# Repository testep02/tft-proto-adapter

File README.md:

TFT-Proto Adapters
=================================================================================
The files in this repository are schematics and boards for use in Eagle that provide an easy connection for the TFT-Proto from MikroE to the STM32F4 Discovery. There are 3 different variations of the board in this repository. All of these designs have been verified to work. They can easily be printed through OshPark.

Features
---------------------------------------------------------------------------------
-  TFT backlight connected to a pin to allow PWM control
-  Backlight powered from 5V instead of 3.3V to allow for brighter viewing
-  Backlight controlled through a transistor to prevent driving the LEDs directly from a pin
-  Reset pin also routed through a transistor and connected to a pin for software control

Variations
---------------------------------------------------------------------------------
-  16-bit FSMC Portrait
	-  This version of the board mounts the TFT in portrait mode
	-  The connection to the STM32F4 Discovery is 16-bit parallel and uses FSMC.
-  16-Bit FSMC Landscape
	-  Same as the above variation, except with this one the board is laid out so that the screen is in landscape configuration. This is the variatioon I use.
-  16-bit GPIO
	-  Uses entire GPIOE port for data lines
	-  Uses sme pins on the GPIOB port for control
	-  IM[3:0] are connected to header pins to allow configuration between 16-bit and 8-bit
	-  Is not connected to the FSMC pins, so bit-banging is required

Code Examples
---------------------------------------------------------------------------------
Examples of driving the TFT-Proto can be found in my other repository. The drivers include all init code and basic drawing functions.

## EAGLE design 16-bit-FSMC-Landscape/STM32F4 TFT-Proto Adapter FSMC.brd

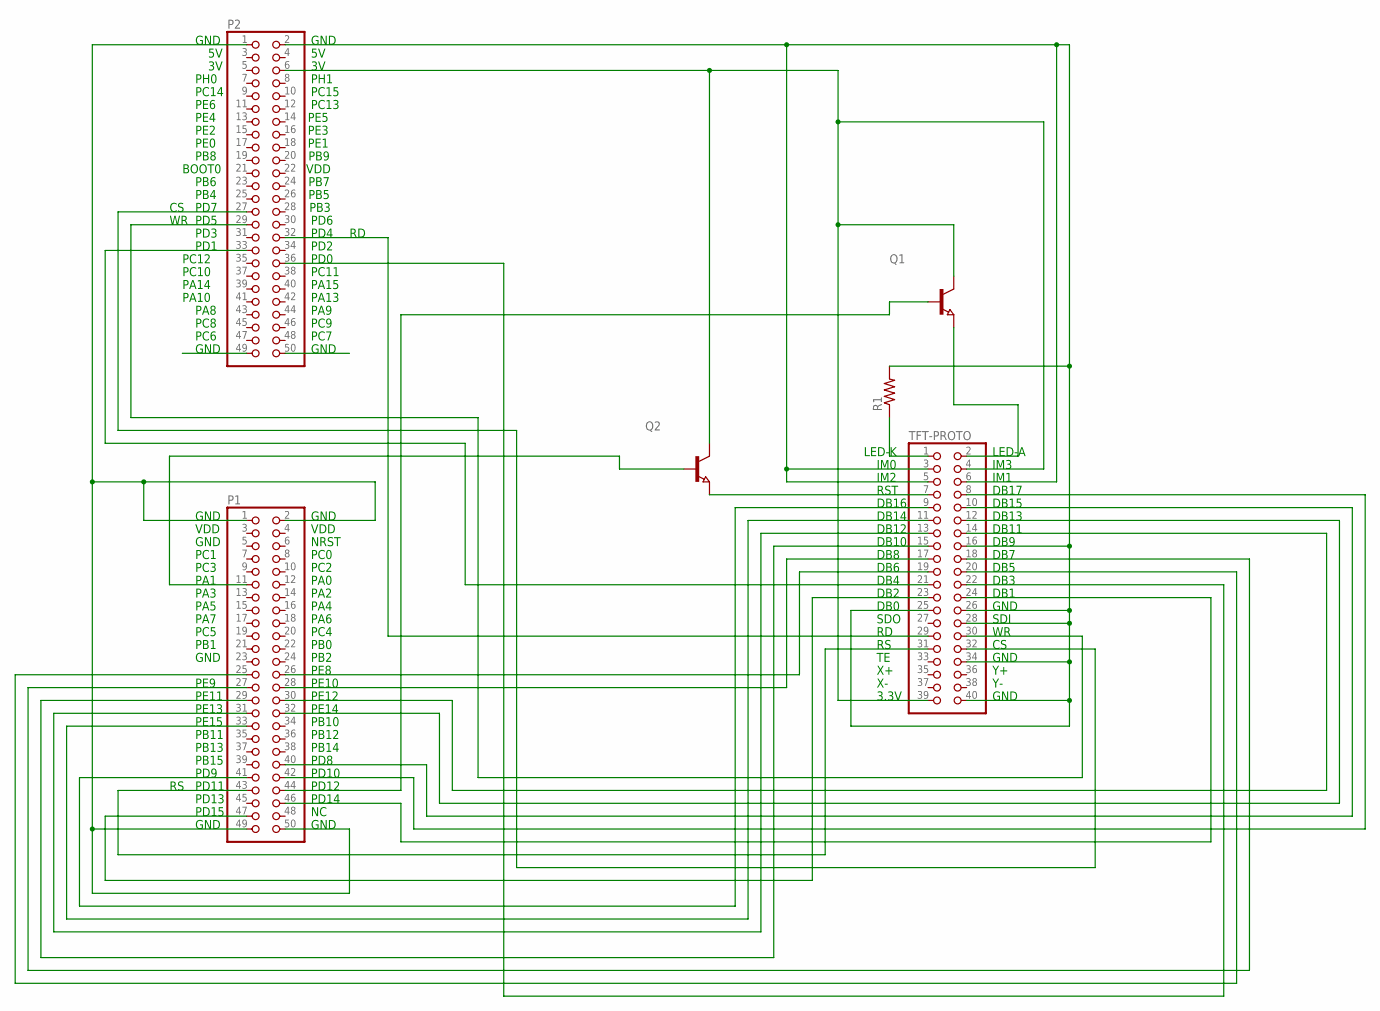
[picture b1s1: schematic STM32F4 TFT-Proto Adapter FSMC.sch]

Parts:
P1, P2: PINHD-2X25; 2X25
Q1, Q2: NPN-TRANSISTOR_SOT23; SOT23
R1: R-US_R0805; R0805
TFT-PROTO: PINHD-2X20; 2X20

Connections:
CS: P2.27, TFT-PROTO.32
DB1: P1.46, TFT-PROTO.24
DB2: P1.47, TFT-PROTO.23
DB3: P2.36, TFT-PROTO.22
DB4: P2.33, TFT-PROTO.21
DB5: P1.25, TFT-PROTO.20
DB6: P1.26, TFT-PROTO.19
DB7: P1.27, TFT-PROTO.18
DB8: P1.28, TFT-PROTO.17
DB10: P1.29, TFT-PROTO.15
DB11: P1.30, TFT-PROTO.14
DB12: P1.31, TFT-PROTO.13
DB13: P1.32, TFT-PROTO.12
DB14: P1.33, TFT-PROTO.11
DB15: P1.40, TFT-PROTO.10
DB16: P1.41, TFT-PROTO.9
DB17: P1.42, TFT-PROTO.8
GND: P1.1, P1.2, P1.49, P1.50, P2.1, P2.2, P2.49, P2.50, R1.2, TFT-PROTO.3, TFT-PROTO.5, TFT-PROTO.6, TFT-PROTO.16, TFT-PROTO.25, TFT-PROTO.26, TFT-PROTO.28, TFT-PROTO.34, TFT-PROTO.40
unnamed: P1.44, Q1.1 (B)
unnamed: R1.1, TFT-PROTO.1
unnamed: Q1.2 (E), TFT-PROTO.2
unnamed: Q2.2 (E), TFT-PROTO.7
PWR: P2.6, Q1.3 (C), Q2.3 (C), TFT-PROTO.4, TFT-PROTO.39
RD: P2.32, TFT-PROTO.29
RS: P1.43, TFT-PROTO.31
RST: P1.11, Q2.1 (B)
WR: P2.29, TFT-PROTO.30

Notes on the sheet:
GND
PH0
PH1
PC14
PC15
PE6
PC13
PE4 PE5
PE2 PE3
PE0 PE1
PB8 PB9
BOOT0 VDD
PB6 PB7
PB4 PB5
PD7 PB3
PD5
PD3
PD1
PC12
PC10
PA14
PA10
PA8
PC8
PC6
PC7
PC9
PA9
PA13
PA15
PC11
PD0
PD2
PD4
PD6
PD15
PD13
PD11
PD9
PB15

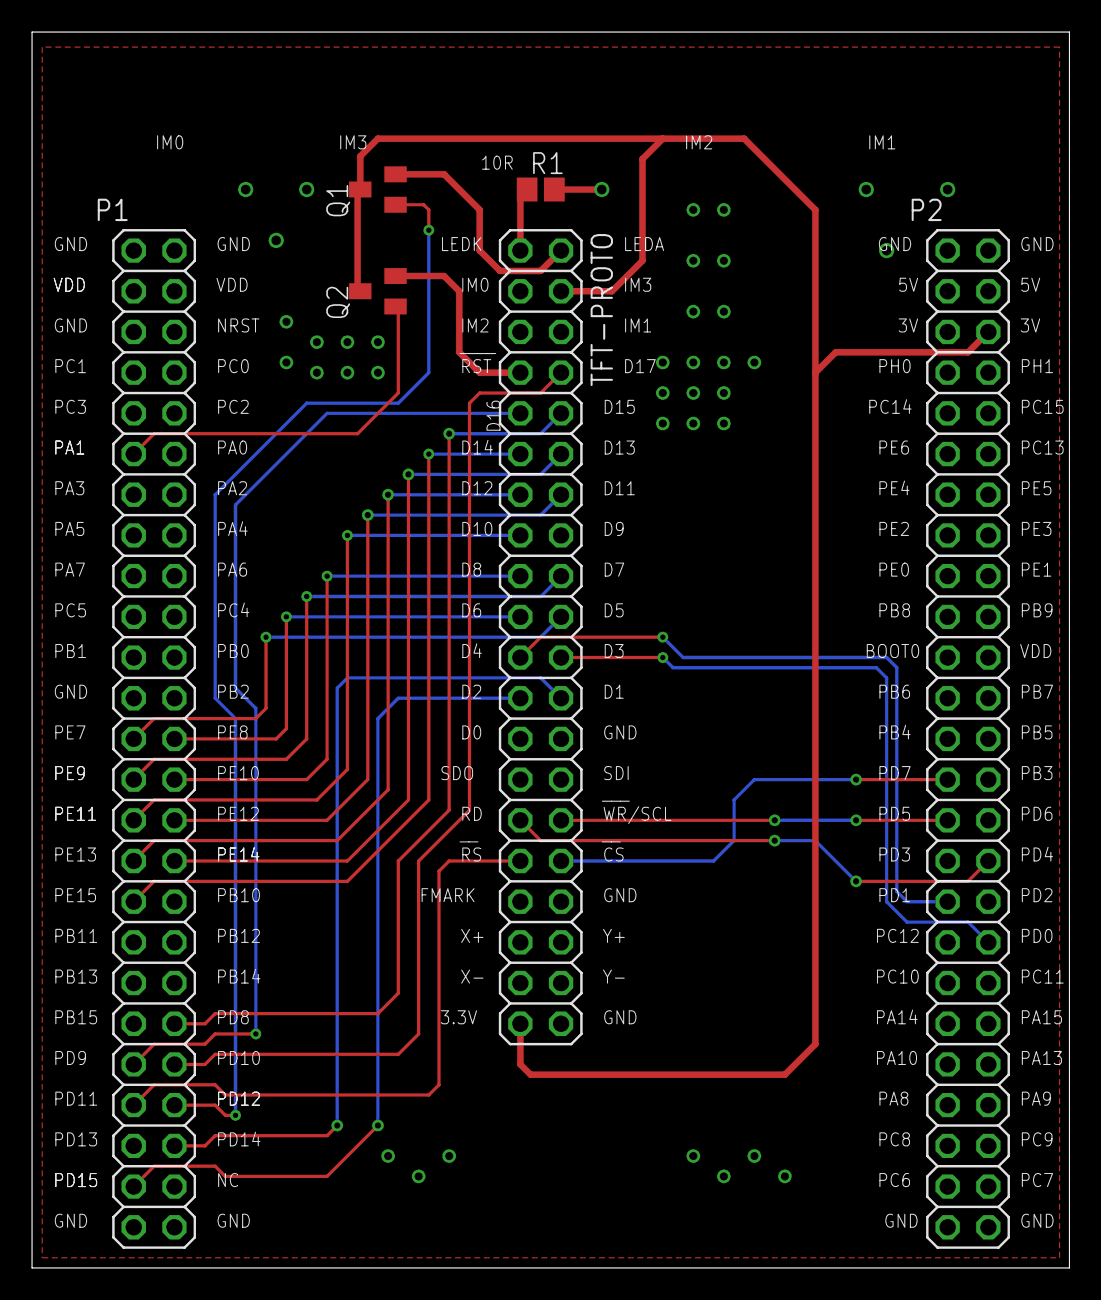
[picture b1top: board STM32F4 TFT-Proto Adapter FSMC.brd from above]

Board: 2 copper layers, 64.8 x 77.1 mm, 6 parts (0 on the bottom side), 27 nets.

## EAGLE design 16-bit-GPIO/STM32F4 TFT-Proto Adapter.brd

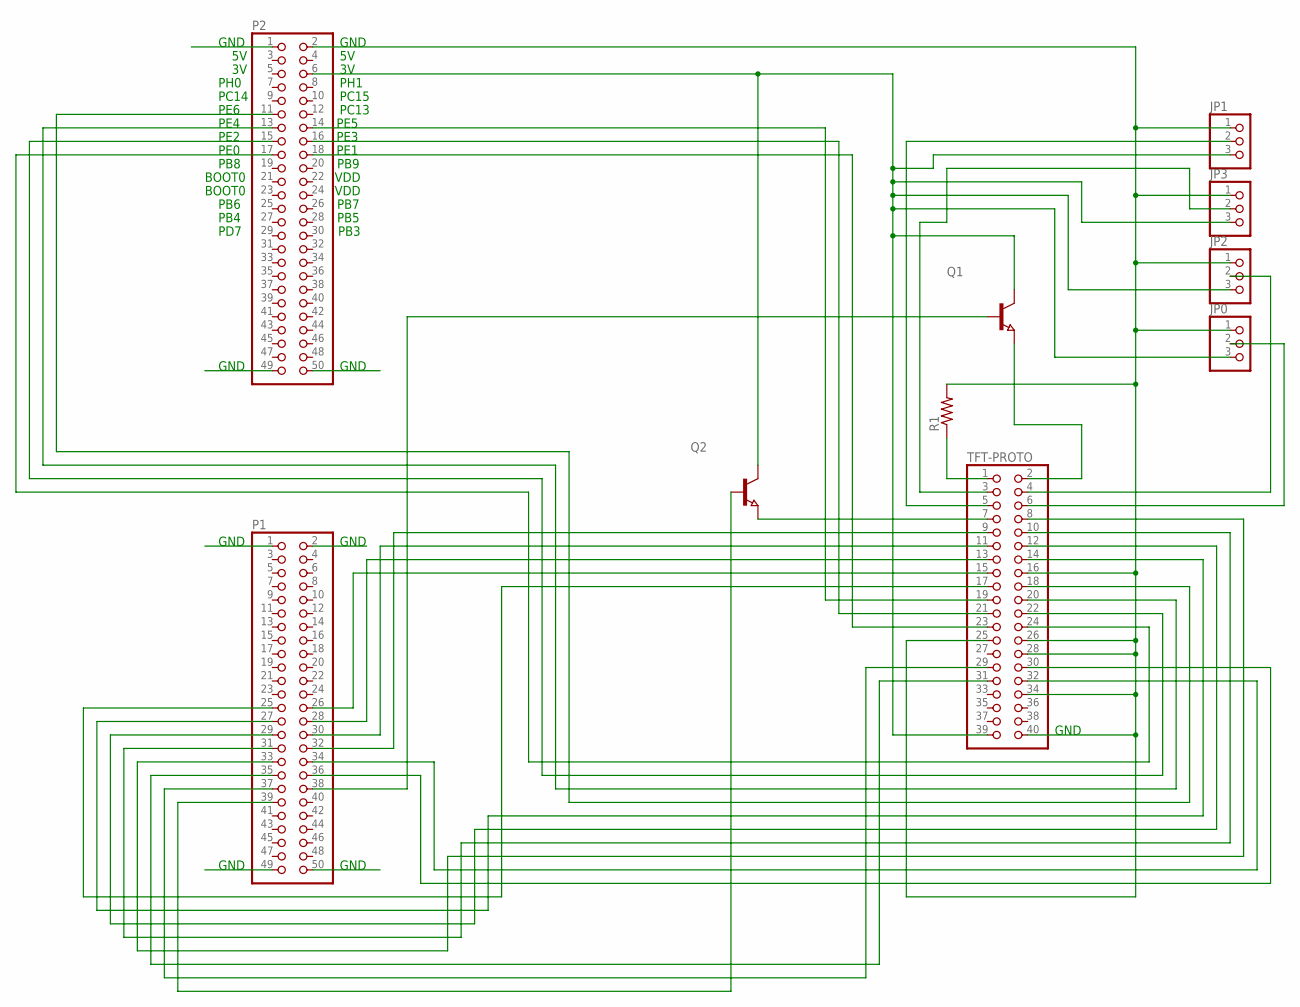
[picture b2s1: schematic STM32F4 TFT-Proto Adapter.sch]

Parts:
JP0, JP1, JP2, JP3: PINHD-1X3; 1X03
P1, P2: PINHD-2X25; 2X25
Q1, Q2: NPN-TRANSISTOR_SOT23; SOT23
R1: R-US_R0805; R0805
TFT-PROTO: PINHD-2X20; 2X20

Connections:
CS: P1.34, TFT-PROTO.32
DAT1: P2.17, TFT-PROTO.24
DAT2: P2.18, TFT-PROTO.23
DAT3: P2.15, TFT-PROTO.22
DAT4: P2.16, TFT-PROTO.21
DAT5: P2.13, TFT-PROTO.20
DAT6: P2.14, TFT-PROTO.19
DAT7: P2.11, TFT-PROTO.18
DAT8: P1.25, TFT-PROTO.17
DAT10: P1.26, TFT-PROTO.15
DAT11: P1.27, TFT-PROTO.14
DAT12: P1.28, TFT-PROTO.13
DAT13: P1.29, TFT-PROTO.12
DAT14: P1.30, TFT-PROTO.11
DAT15: P1.31, TFT-PROTO.10
DAT16: P1.32, TFT-PROTO.9
DAT17: P1.33, TFT-PROTO.8
GND: JP0.1, JP1.1, JP2.1, JP3.1, P1.1, P1.2, P1.49, P1.50, P2.1, P2.2, P2.49, P2.50, R1.2, TFT-PROTO.16, TFT-PROTO.25, TFT-PROTO.26, TFT-PROTO.28, TFT-PROTO.34, TFT-PROTO.40
IM0: JP3.2, TFT-PROTO.3
IM1: JP0.2, TFT-PROTO.6
IM2: JP1.2, TFT-PROTO.5
IM3: JP2.2, TFT-PROTO.4
LEDA: P1.38, Q1.1 (B)
unnamed: R1.1, TFT-PROTO.1
unnamed: Q1.2 (E), TFT-PROTO.2
unnamed: Q2.2 (E), TFT-PROTO.7
PWR: JP0.3, JP1.3, JP2.3, JP3.3, P2.6, Q1.3 (C), Q2.3 (C), TFT-PROTO.39
RD: P1.37, TFT-PROTO.29
RS: P1.35, TFT-PROTO.31
RST: P1.39, Q2.1 (B)
WR: P1.36, TFT-PROTO.30

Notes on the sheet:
GND
PH0
PH1
PC14
PC15
PE6
PC13
PE4 PE5
PE2 PE3
PE0 PE1
PB8 PB9
BOOT0 VDD
PB6 PB7
PB4 PB5
PD7 PB3

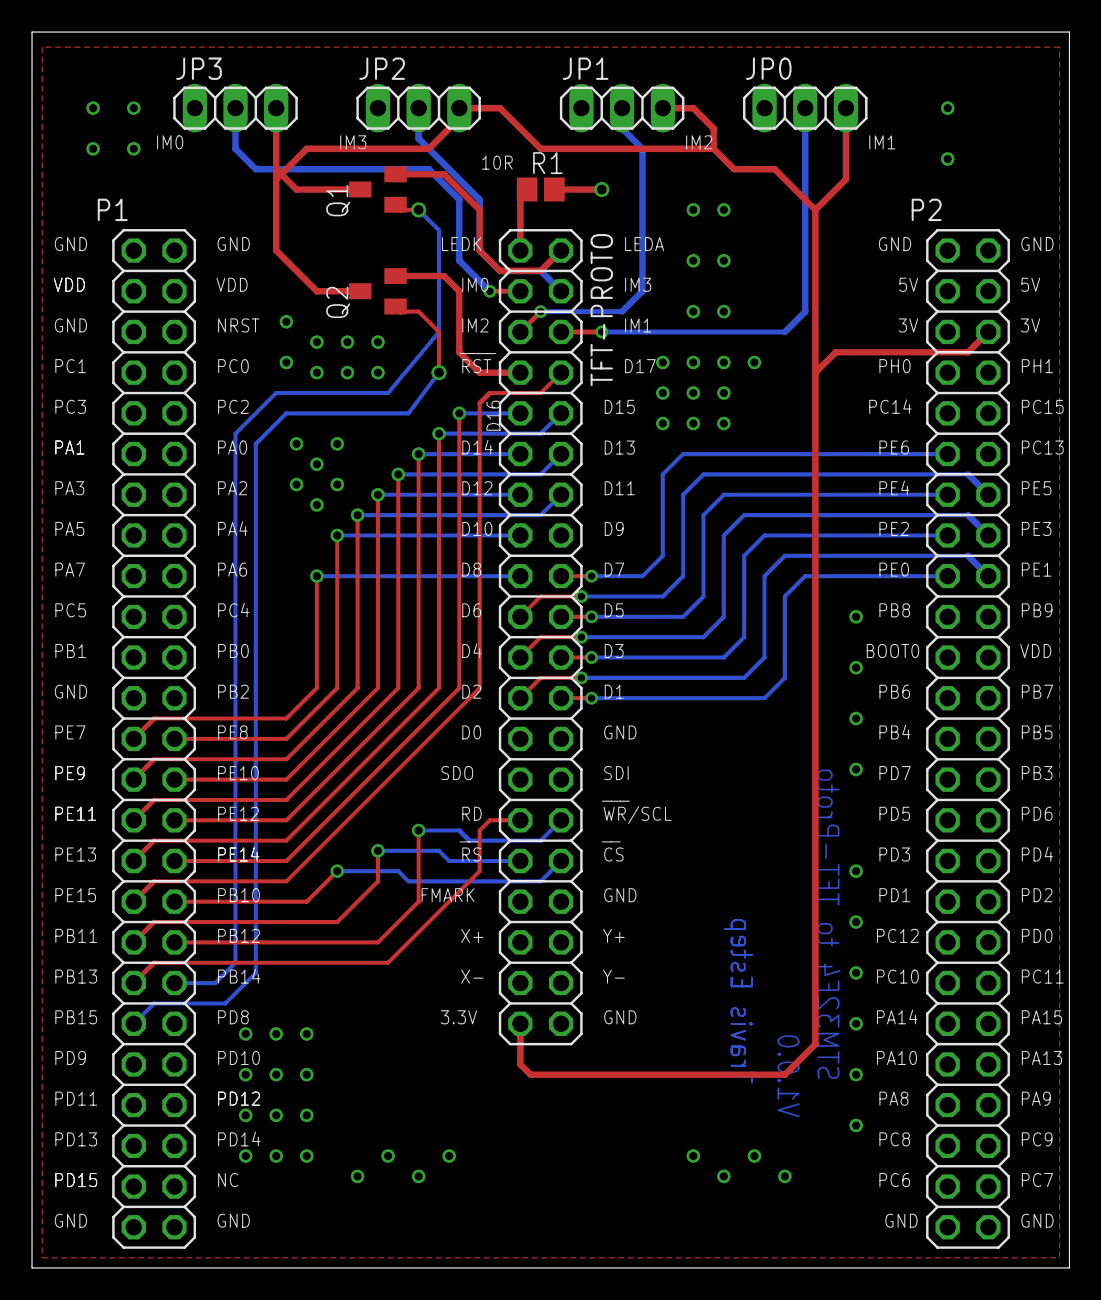
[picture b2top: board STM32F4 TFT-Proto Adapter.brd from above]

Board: 2 copper layers, 64.8 x 77.1 mm, 10 parts (0 on the bottom side), 31 nets.

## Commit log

2013-11-26 Initial commit of PCB Designs
2013-11-27 Added text to README file
2013-11-27 Modified README.md
